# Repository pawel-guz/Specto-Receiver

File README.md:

# Specto-Receiver
Source code for a DIY micro-board receiver for [Specto Music Visualizer](https://github.com/pawel-guz/Specto/blob/master/readme.md#specto-music--visualizer).

## Board and circuit
This code is compatible with NodeMCU v1.0 boards. It should also work with other boards based on ESP8266 WiFI modules. 
Basic functionality - connecting with PC over SerialPort will work with every Arduino-like board. 

If you look for simple solution see: [simple circuit instructions](https://github.com/pawel-guz/Specto/blob/master/readme.md#example-circuit).

## To do:
``` 
- Final testing.
- Design and test PCB.
```

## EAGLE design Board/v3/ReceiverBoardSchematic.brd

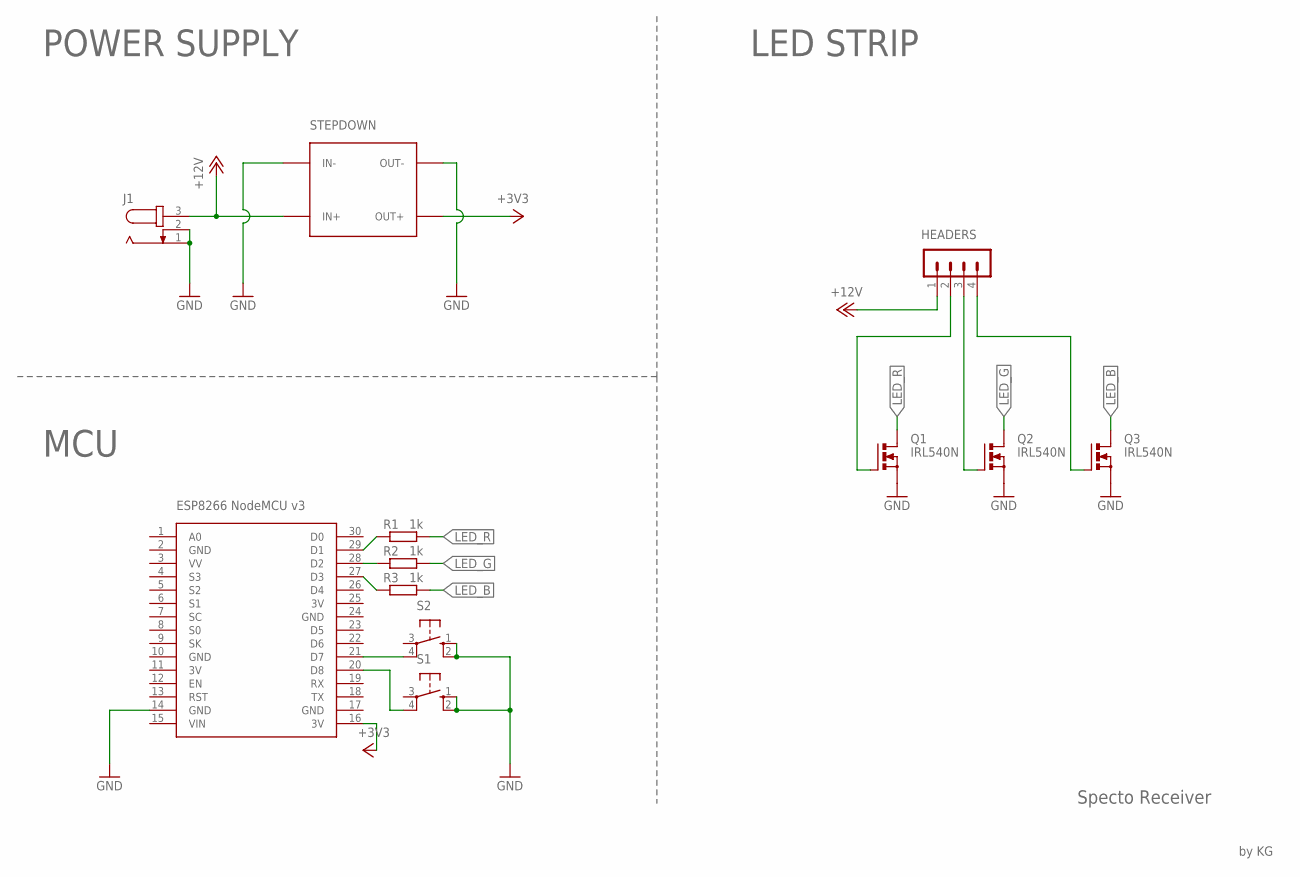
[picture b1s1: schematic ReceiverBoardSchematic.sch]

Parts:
ESP2866: NODEMCU
HEADERS: MA04-1
J1: JACK-PLUG1; SPC4078
Q1, Q2, Q3: IRL540N; TO220BV
R1, R2, R3: 1k; 0309/12
S1, S2: 10-XX; B3F-10XX
STEPDOWN: DC-DC-STEP-DOWN-MP2307

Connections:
3V: ESP2866.11 (3V), ESP2866.25 (3V)
+3V3: ESP2866.16 (3V), STEPDOWN.OUT+
+12V: HEADERS.1, J1.3, STEPDOWN.IN+
GND: ESP2866.2 (GND), ESP2866.10 (GND), ESP2866.14 (GND), ESP2866.17 (GND), ESP2866.24 (GND), J1.1, J1.2, Q1.S, Q2.S, Q3.S, S1.1 (S), S1.2 (S1), S2.1 (S), S2.2 (S1), STEPDOWN.IN-, STEPDOWN.OUT-
LED_B: Q3.D, R3.2
LED_G: Q2.D, R2.2
LED_R: Q1.D, R1.2
unnamed: HEADERS.2, Q1.G
unnamed: HEADERS.3, Q2.G
unnamed: HEADERS.4, Q3.G
unnamed: ESP2866.29 (D1), R1.1
unnamed: ESP2866.28 (D2), R2.1
unnamed: ESP2866.27 (D3), R3.1
unnamed: ESP2866.21 (D7), S2.4 (P1)
S1: ESP2866.20 (D8), S1.4 (P1)

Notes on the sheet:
by KG
Specto Receiver
POWER SUPPLY
MCU
LED STRIP
ESP8266 NodeMCU v3

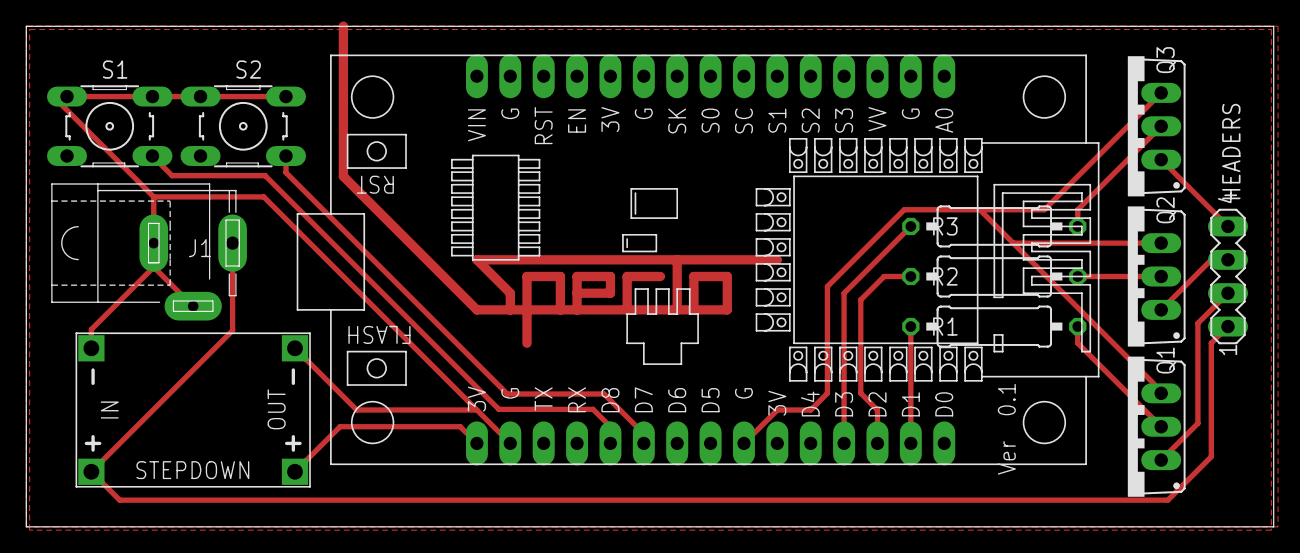
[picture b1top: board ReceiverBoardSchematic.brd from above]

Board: 2 copper layers, 94.9 x 38.1 mm, 12 parts (0 on the bottom side), 15 nets.

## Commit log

2019-11-28 Boards
2019-12-07 071219
2019-12-16 WIFI&notifications update

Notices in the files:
parts and their libraries:
diy-modules: Released under the Creative Commons Attribution 4.0 International License: http://creativecommons.org/licenses/by/4.0
